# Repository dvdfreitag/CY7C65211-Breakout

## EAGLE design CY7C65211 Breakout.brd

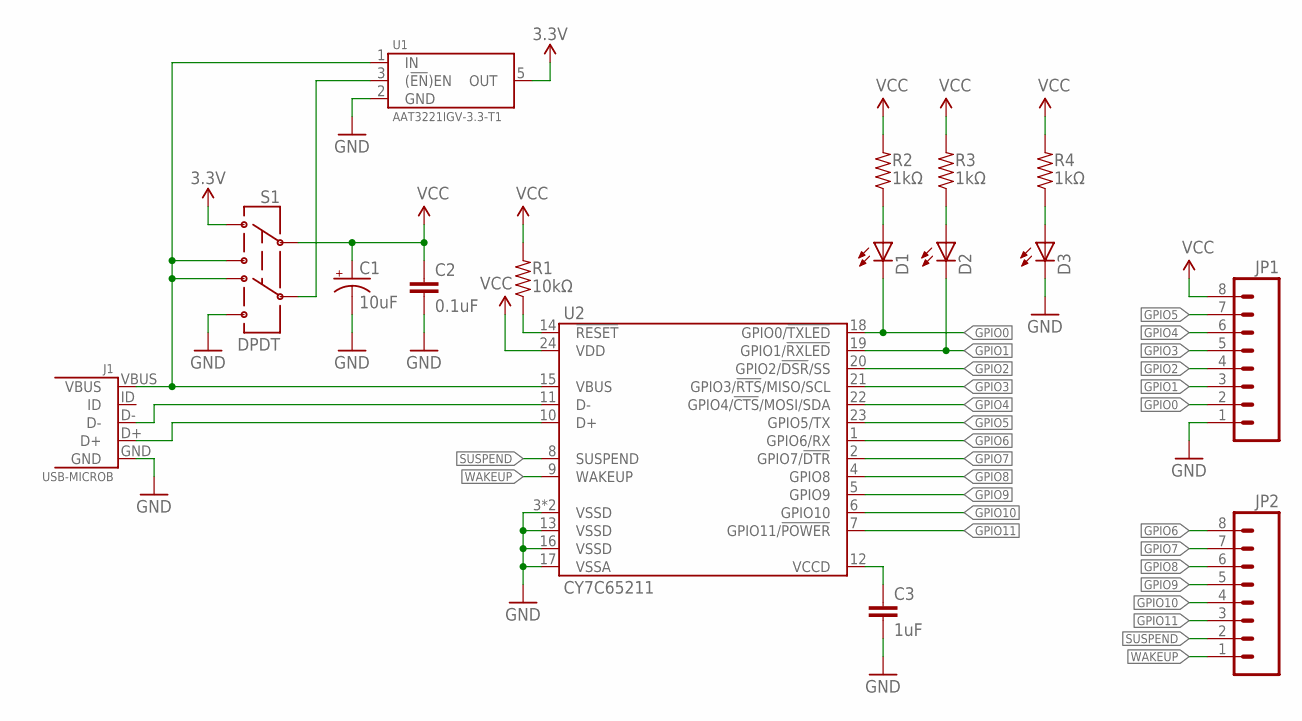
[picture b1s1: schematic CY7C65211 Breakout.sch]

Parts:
C1: 10uF; 0805-CAP_POL
C2: 0.1uF; 0402-CAP
C3: 1uF; 0402-CAP
D1, D2, D3: LED0603; LED-0603
J1: USB-MICROB
JP1, JP2: M081X08; 1X08
R1: 10kΩ; 0402-RES
R2, R3, R4: 1kΩ; 0402-RES
S1: DPDT; AYZ0202
U1: AAT3221IGV-3.3-T1; SOT23-5
U2: CY7C65211; QFN-24

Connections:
3.3V: S1.1, U1.5 (OUT)
GND: C1.C (-), C2.2, C3.2, D3.C, J1.GND, JP1.1, S1.6, U1.2 (GND), U2.3 (VSSD), U2.13 (VSSD), U2.16 (VSSD), U2.17 (VSSA), U2.EP (VSSD)
GPIO0: D1.C, JP1.2, U2.18 (GPIO0/!TXLED)
GPIO1: D2.C, JP1.3, U2.19 (GPIO1/!RXLED)
GPIO2: JP1.4, U2.20 (GPIO2/!DSR!/SS)
GPIO3: JP1.5, U2.21 (GPIO3/!RTS!/MISO/SCL)
GPIO4: JP1.6, U2.22 (GPIO4/!CTS!/MOSI/SDA)
GPIO5: JP1.7, U2.23 (GPIO5/TX)
GPIO6: JP2.8, U2.1 (GPIO6/RX)
GPIO7: JP2.7, U2.2 (GPIO7/!DTR)
GPIO8: JP2.6, U2.4 (GPIO8)
GPIO9: JP2.5, U2.5 (GPIO9)
GPIO10: JP2.4, U2.6 (GPIO10)
GPIO11: JP2.3, U2.7 (GPIO11/!POWER)
unnamed: J1.VBUS, S1.3, S1.4, U1.1 (IN), U2.15 (VBUS)
unnamed: J1.D-, U2.11 (D-)
unnamed: J1.D+, U2.10 (D+)
unnamed: S1.5, U1.3 ((!EN!)EN)
unnamed: D2.A, R3.1
unnamed: R1.1, U2.14 (!RESET)
unnamed: C3.1, U2.12 (VCCD)
unnamed: D1.A, R2.1
unnamed: D3.A, R4.1
SUSPEND: JP2.2, U2.8 (SUSPEND)
VCC: C1.A (+), C2.1, JP1.8, R1.2, R2.2, R3.2, R4.2, S1.2, U2.24 (VDD)
WAKEUP: JP2.1, U2.9 (WAKEUP)

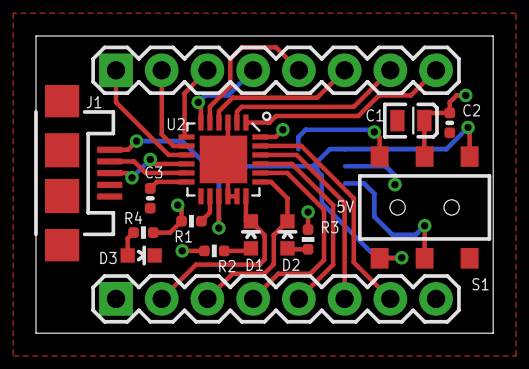
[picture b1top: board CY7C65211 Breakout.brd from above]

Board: 2 copper layers, 25.4 x 16.5 mm, 16 parts (1 on the bottom side), 26 nets.

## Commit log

2016-08-12 Create LICENSE
2016-08-12 Added pdf documents

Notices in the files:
parts and their libraries:
SparkFun-Electromechanical: Licensing: CC v3.0 Share-Alike You are welcome to use this library for commercial purposes.
